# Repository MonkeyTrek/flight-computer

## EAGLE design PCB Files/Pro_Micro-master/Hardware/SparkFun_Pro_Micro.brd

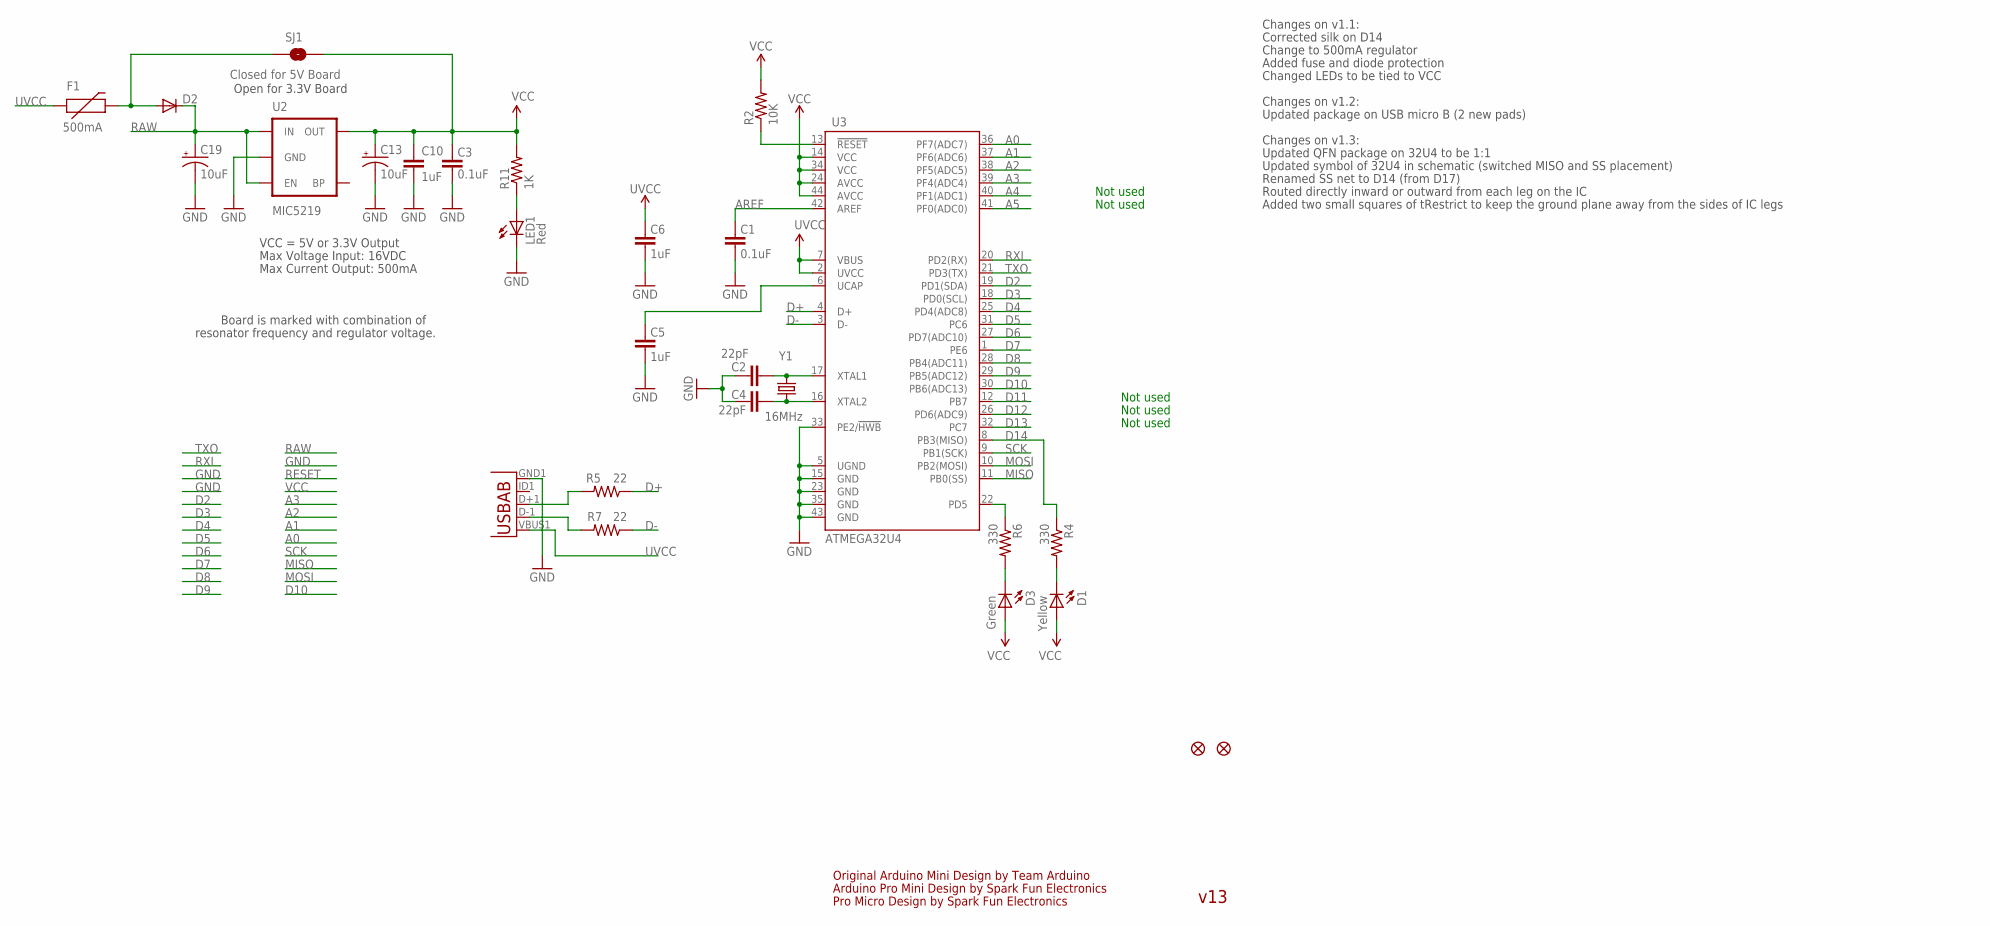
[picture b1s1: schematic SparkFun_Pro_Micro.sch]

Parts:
C1, C3: 0.1uF; 0603-CAP
C2, C4: 22pF; 0603-CAP
C5, C6, C10: 1uF; 0603-CAP
C13, C19: 10uF; EIA3216
D1: Yellow; LED-0603
D2: DIODESOD; SOD-323
D3: Green; LED-0603
F1: 500mA; PTC-1206
JP1, JP2: FIDUCIALUFIDUCIAL; MICRO-FIDUCIAL
LED1: Red; LED-0603
R2: 10K; 0603-RES
R4, R6: 330; 0603-RES
R5, R7: 22; 0603-RES
R11: 1K; 0603-RES
SJ1: Closed for 5V Board; SJ_2S
U2: MIC5219; SOT23-5
U3: ATMEGA32U4; QFN-44-NOPAD_1:1-OUTFAKES
X1: USB-ABIN&OUT; USB-AB-MICRO-SMD-V03-IN&OUT
Y1: 16MHz; CRYSTAL-SMD-5X3

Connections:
A0: U3.36 (PF7(ADC7))
A1: U3.37 (PF6(ADC6))
A2: U3.38 (PF5(ADC5))
A3: U3.39 (PF4(ADC4))
A4: U3.40 (PF1(ADC1))
A5: U3.41 (PF0(ADC0))
AREF: C1.2, U3.42 (AREF)
D2: U3.19 (PD1(SDA))
D3: U3.18 (PD0(SCL))
D4: U3.25 (PD4(ADC8))
D5: U3.31 (PC6)
D6: U3.27 (PD7(ADC10))
D7: U3.1 (PE6)
D8: U3.28 (PB4(ADC11))
D9: U3.29 (PB5(ADC12))
D10: U3.30 (PB6(ADC13))
D11: U3.12 (PB7)
D12: U3.26 (PD6(ADC9))
D13: U3.32 (PC7)
D14: R4.1, U3.8 (PB3(MISO))
D+: R5.1, U3.4 (D+)
D-: R7.1, U3.3 (D-)
GND: C1.1, C2.2, C3.1, C4.2, C5.1, C6.1, C10.2, C13.C (-), C19.C (-), LED1.C, U2.2 (GND), U3.5 (UGND), U3.15 (GND), U3.23 (GND), U3.33 (PE2/!HWB), U3.35 (GND), U3.43 (GND), X1.GND1 (GND)
MISO: U3.11 (PB0(SS))
MOSI: U3.10 (PB2(MOSI))
unnamed: C4.1, U3.16 (XTAL2), Y1.1
unnamed: C2.1, U3.17 (XTAL1), Y1.3 (2)
unnamed: D2.2 (A), F1.2, SJ1.1
unnamed: C5.2, U3.6 (UCAP)
unnamed: D1.C, R4.2
unnamed: R7.2, X1.D-1 (D-)
unnamed: D3.C, R6.2
unnamed: R5.2, X1.D+1 (D+)
unnamed: LED1.A, R11.1
RAW: C19.A (+), D2.1 (C), U2.1 (IN), U2.3 (EN)
RESET: R2.1, U3.13 (!RESET)
RXI: U3.20 (PD2(RX))
SCK: U3.9 (PB1(SCK))
TXLED: R6.1, U3.22 (PD5)
TXO: U3.21 (PD3(TX))
UVCC: C6.2, F1.1, U3.2 (UVCC), U3.7 (VBUS), X1.VBUS1 (VBUS)
VCC: C3.2, C10.1, C13.A (+), D1.A, D3.A, R2.2, R11.2, SJ1.2, U2.5 (OUT), U3.14 (VCC), U3.24 (AVCC), U3.34 (VCC), U3.44 (AVCC)

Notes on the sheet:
Original Arduino Mini Design by Team Arduino
Arduino Pro Mini Design by Spark Fun Electronics
Max Voltage Input: 16VDC
Max Current Output: 500mA
Board is marked with combination of
resonator frequency and regulator voltage.
VCC = 5V or 3.3V Output
Not used
Pro Micro Design by Spark Fun Electronics
Changes on v1.1:
Corrected silk on D14
Change to 500mA regulator
Open for 3.3V Board
Added fuse and diode protection
Changed LEDs to be tied to VCC
Changes on v1.2:
Updated package on USB micro B (2 new pads)
Changes on v1.3:
Updated QFN package on 32U4 to be 1:1
Updated symbol of 32U4 in schematic (switched MISO and SS placement)
Renamed SS net to D14 (from D17)
Routed directly inward or outward from each leg on the IC
Added two small squares of tRestrict to keep the ground plane away from the sides of IC legs
v13

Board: 2 copper layers, 27 parts (0 on the bottom side), 19 nets, no tracks yet.

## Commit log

2021-05-29 first push with board files
